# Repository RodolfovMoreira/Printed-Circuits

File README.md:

# Printed-Circuits
Files from the elective exercices

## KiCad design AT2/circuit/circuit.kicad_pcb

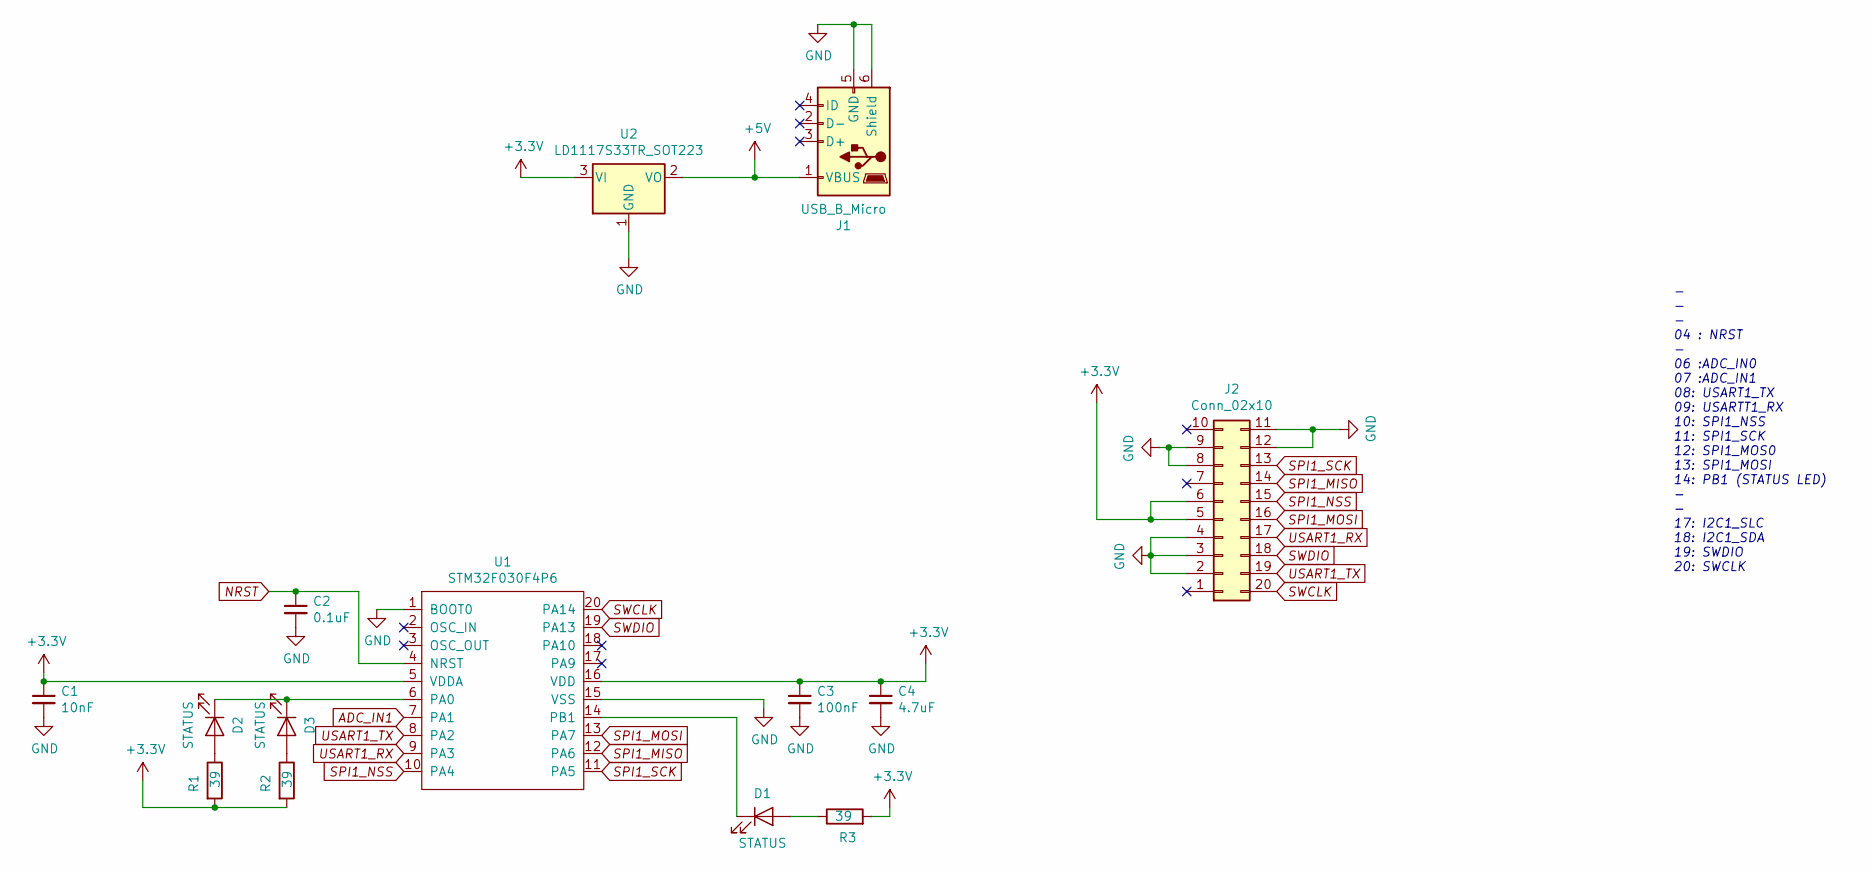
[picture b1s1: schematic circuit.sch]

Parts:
C1: 10nF; C_0805_2012Metric
C2: 0.1uF; C_0805_2012Metric
C3: 100nF; C_0805_2012Metric
C4: 4.7uF; C_0805_2012Metric
D1, D2, D3: STATUS; LED_0805_2012Metric_Castellated
J1: USB_B_Micro; USB_Micro-B_Molex-105133-0001
J2: Conn_02x10; PinHeader_2x10_P1.00mm_Vertical_SMD
R1, R2, R3: 39; R_0805_2012Metric
U1: STM32F030F4P6; HTSSOP-20-1EP_4.4x6.5mm_P0.65mm_EP3.4x6.5mm_ThermalVias
U2: LD1117S33TR_SOT223; SOT-223-3_TabPin2

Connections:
+3V3: C1.1, C3.1, C4.1, J2.5, J2.6, R1.2, R2.2, R3.2, U1.5 (VDDA), U1.16 (VDD), U2.3 (VI)
+5V: J1.1 (VBUS), U2.2 (VO)
ADC_IN1: U1.7 (PA1)
GND: C1.2, C2.2, C3.2, C4.2, J1.5 (GND), J1.6 (Shield), J2.2, J2.3, J2.4, J2.8, J2.9, J2.11, J2.12, U1.1 (BOOT0), U1.15 (VSS), U2.1 (GND)
NRST: C2.1, U1.4 (NRST)
unnamed: D1.1 (K), U1.14 (PB1)
unnamed: D1.2 (A), R3.1
unnamed: D2.1 (K), D3.1 (K), U1.6 (PA0)
unnamed: D2.2 (A), R1.1
unnamed: D3.2 (A), R2.1
SPI1_MISO: J2.14, U1.12 (PA6)
SPI1_MOSI: J2.16, U1.13 (PA7)
SPI1_NSS: J2.15, U1.10 (PA4)
SPI1_SCK: J2.13, U1.11 (PA5)
SWCLK: J2.20, U1.20 (PA14)
SWDIO: J2.18, U1.19 (PA13)
USART1_RX: J2.17, U1.9 (PA3)
USART1_TX: J2.19, U1.8 (PA2)

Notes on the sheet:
- - - 04 : NRST - 06 :ADC_IN0 07 :ADC_IN1 08: USART1_TX 09: USARTT1_RX 10: SPI1_NSS 11: SPI1_SCK 12: SPI1_MOS0 13: SPI1_MOSI 14: PB1 (STATUS LED) - - 17: I2C1_SLC 18: I2C1_SDA 19: SWDIO 20: SWCLK

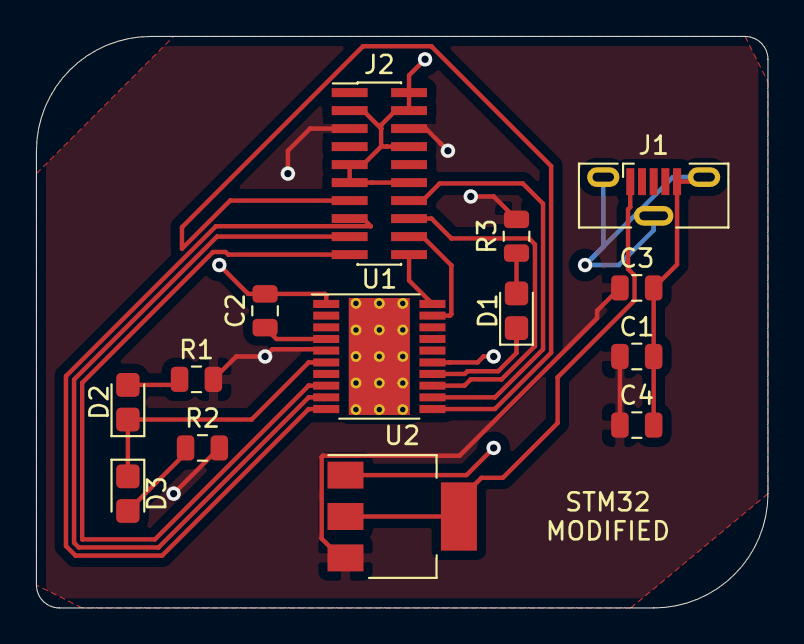
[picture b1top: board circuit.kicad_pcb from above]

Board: 2 copper layers, 40.6 x 31.8 mm, 14 parts (0 on the bottom side), 17 nets.

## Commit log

2019-11-17 Commiting Old files
